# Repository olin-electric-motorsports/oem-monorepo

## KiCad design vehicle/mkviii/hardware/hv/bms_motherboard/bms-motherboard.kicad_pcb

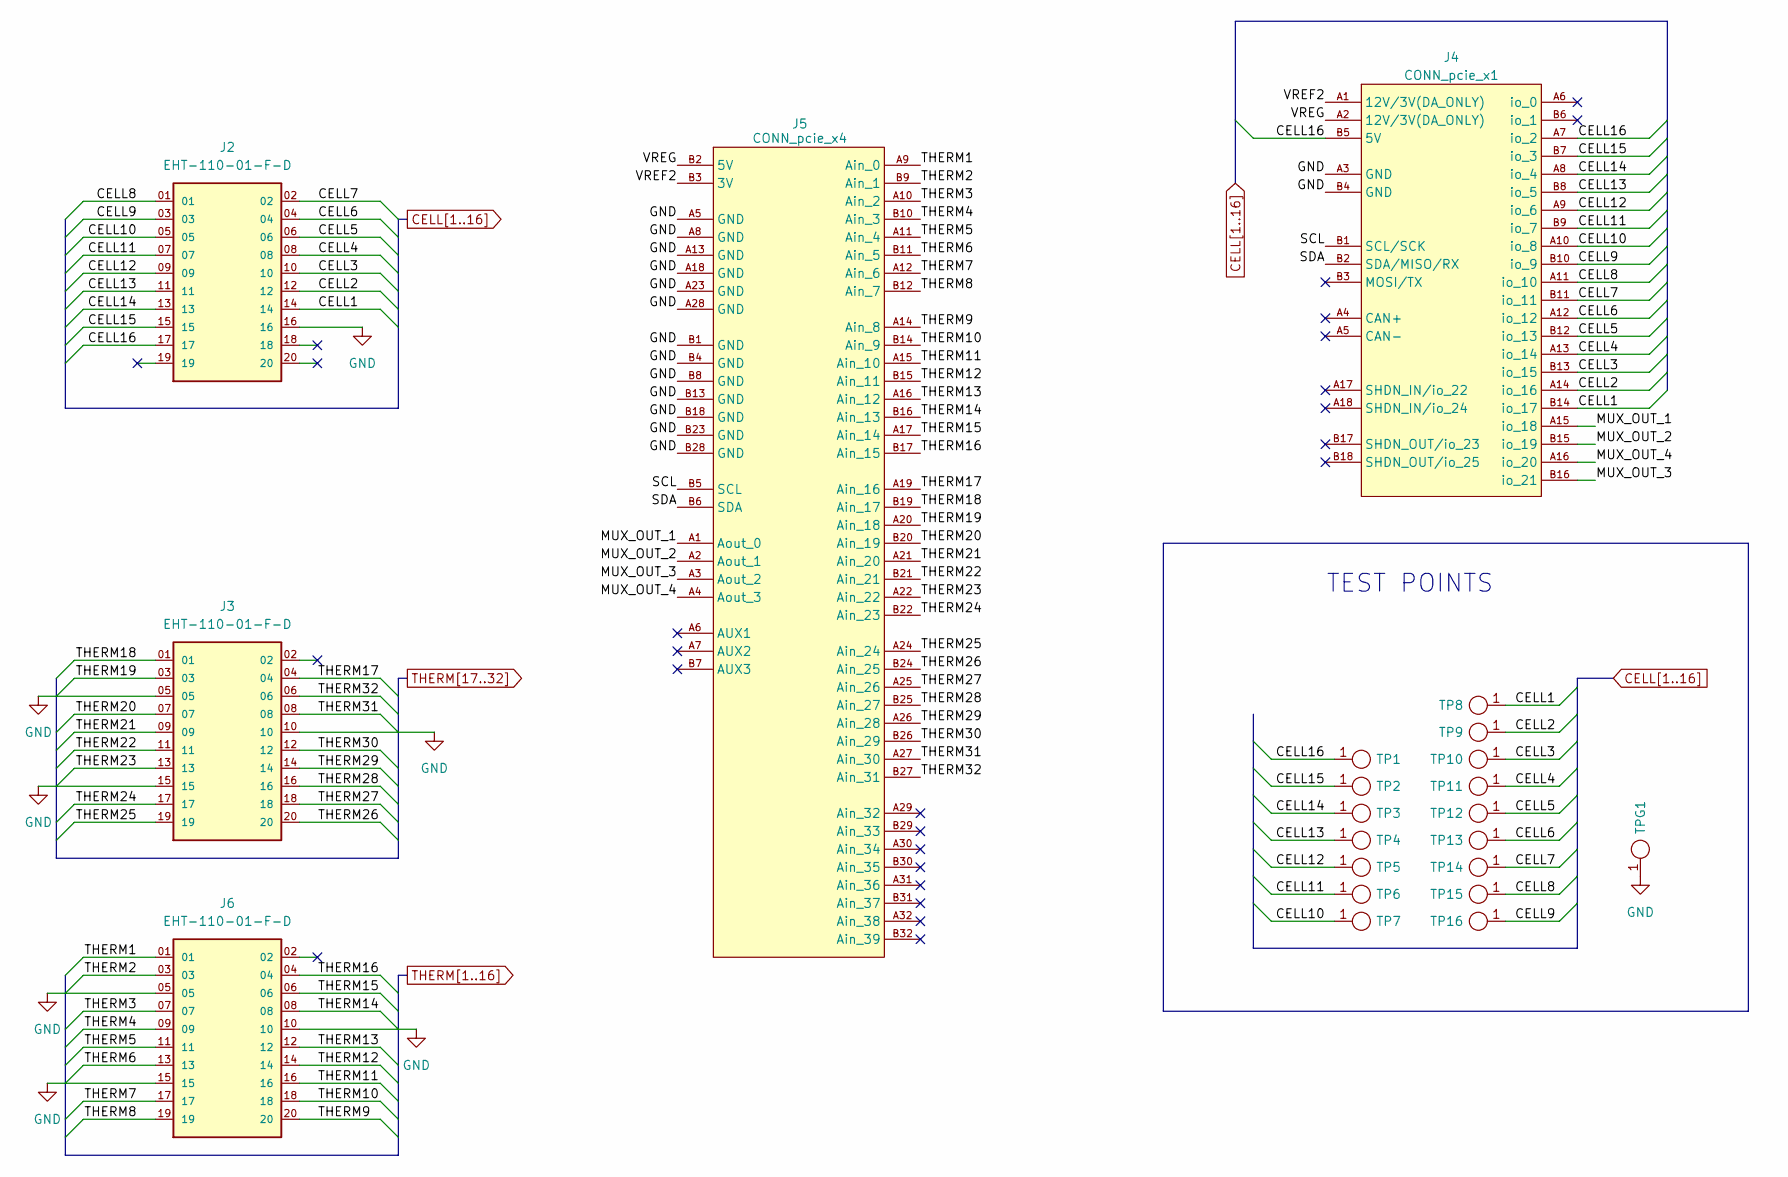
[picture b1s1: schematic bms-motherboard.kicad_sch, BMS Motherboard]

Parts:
J2, J3, J6: EHT-110-01-F-D; SAMTEC_EHT-110-01-X-D (J_EHT-110-01-F-D); MPN EHT-110-01-F-D
J4: CONN_pcie_x1; te_pcie_x1_connector
J5: CONN_pcie_x4; te_pcie_x4_connector
TP1, TP2, TP3, TP4, TP5, TP6, TP7, TP8, TP9, TP10, TP11, TP12, TP13, TP14, TP15, TP16: TP_SMD; Test_Point_SMD; MPN 5019
TPG1: TP_SMD; Test_Point_SMD; MPN 5019

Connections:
/MUX_OUT_1: J4.A15 (io_18), J5.A1 (Aout_0)
/MUX_OUT_2: J4.B15 (io_19), J5.A2 (Aout_1)
/MUX_OUT_3: J4.B16 (io_21), J5.A3 (Aout_2)
/MUX_OUT_4: J4.A16 (io_20), J5.A4 (Aout_3)
/SCL: J4.B1 (SCL/SCK), J5.B5 (SCL)
/SDA: J4.B2 (SDA/MISO/RX), J5.B6 (SDA)
/VREF2: J4.A1 (12V/3V(DA_ONLY)), J5.B3 (3V)
/VREG: J4.A2 (12V/3V(DA_ONLY)), J5.B2 (5V)
CELL1: J2.14, J4.B14 (io_17), TP8.1
CELL2: J2.12, J4.A14 (io_16), TP9.1
CELL3: J2.10, J4.B13 (io_15), TP10.1
CELL4: J2.08, J4.A13 (io_14), TP11.1
CELL5: J2.06, J4.B12 (io_13), TP12.1
CELL6: J2.04, J4.A12 (io_12), TP13.1
CELL7: J2.02, J4.B11 (io_11), TP14.1
CELL8: J2.01, J4.A11 (io_10), TP15.1
CELL9: J2.03, J4.B10 (io_9), TP16.1
CELL10: J2.05, J4.A10 (io_8), TP7.1
CELL11: J2.07, J4.B9 (io_7), TP6.1
CELL12: J2.09, J4.A9 (io_6), TP5.1
CELL13: J2.11, J4.B8 (io_5), TP4.1
CELL14: J2.13, J4.A8 (io_4), TP3.1
CELL15: J2.15, J4.B7 (io_3), TP2.1
CELL16: J2.17, J4.A7 (io_2), J4.B5 (5V), TP1.1
GND: J2.16, J3.05, J3.10, J3.15, J4.A3 (GND), J4.B4 (GND), J5.A5 (GND), J5.A8 (GND), J5.A13 (GND), J5.A18 (GND), J5.A23 (GND), J5.A28 (GND), J5.B1 (GND), J5.B4 (GND), J5.B8 (GND), J5.B13 (GND), J5.B18 (GND), J5.B23 (GND), J5.B28 (GND), J6.05, J6.10, J6.15, TPG1.1
THERM1: J5.A9 (Ain_0), J6.01
THERM2: J5.B9 (Ain_1), J6.03
THERM3: J5.A10 (Ain_2), J6.07
THERM4: J5.B10 (Ain_3), J6.09
THERM5: J5.A11 (Ain_4), J6.11
THERM6: J5.B11 (Ain_5), J6.13
THERM7: J5.A12 (Ain_6), J6.17
THERM8: J5.B12 (Ain_7), J6.19
THERM9: J5.A14 (Ain_8), J6.20
THERM10: J5.B14 (Ain_9), J6.18
THERM11: J5.A15 (Ain_10), J6.16
THERM12: J5.B15 (Ain_11), J6.14
THERM13: J5.A16 (Ain_12), J6.12
THERM14: J5.B16 (Ain_13), J6.08
THERM15: J5.A17 (Ain_14), J6.06
THERM16: J5.B17 (Ain_15), J6.04
THERM17: J3.04, J5.A19 (Ain_16)
THERM18: J3.01, J5.B19 (Ain_17)
THERM19: J3.03, J5.A20 (Ain_18)
THERM20: J3.07, J5.B20 (Ain_19)
THERM21: J3.09, J5.A21 (Ain_20)
THERM22: J3.11, J5.B21 (Ain_21)
THERM23: J3.13, J5.A22 (Ain_22)
THERM24: J3.17, J5.B22 (Ain_23)
THERM25: J3.19, J5.A24 (Ain_24)
THERM26: J3.20, J5.B24 (Ain_25)
THERM27: J3.18, J5.A25 (Ain_26)
THERM28: J3.16, J5.B25 (Ain_27)
THERM29: J3.14, J5.A26 (Ain_28)
THERM30: J3.12, J5.B26 (Ain_29)
THERM31: J3.08, J5.A27 (Ain_30)
THERM32: J3.06, J5.B27 (Ain_31)

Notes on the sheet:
TEST POINTS

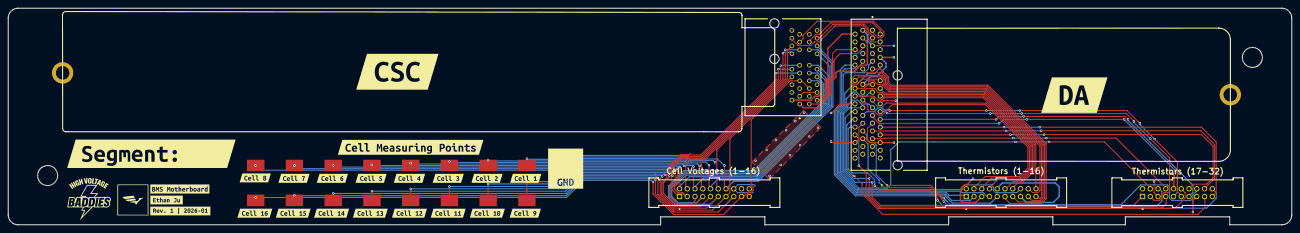
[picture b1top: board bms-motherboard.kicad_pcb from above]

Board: 2 copper layers, 331.3 x 55.9 mm, 48 parts (0 on the bottom side), 57 nets.

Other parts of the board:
H1, H2: CONN_MountingHole; PCIe_Mount
kibuzzard-691BC298: G***; kibuzzard-691BC298
kibuzzard-6747A1EF: G***; kibuzzard-6747A1EF
kibuzzard-6747A1F5: G***; kibuzzard-6747A1F5
kibuzzard-6747A1FA: G***; kibuzzard-6747A1FA
kibuzzard-6747A20D: G***; kibuzzard-6747A20D
kibuzzard-6747A21A: G***; kibuzzard-6747A21A
kibuzzard-6747A21D: G***; kibuzzard-6747A21D
kibuzzard-6747A22C: G***; kibuzzard-6747A22C
kibuzzard-6747A22F: G***; kibuzzard-6747A22F
kibuzzard-6747A069: G***; kibuzzard-6747A069
kibuzzard-6747A200: G***; kibuzzard-6747A200
kibuzzard-6747A204: G***; kibuzzard-6747A204
kibuzzard-6747A209: G***; kibuzzard-6747A209
kibuzzard-6747A211: G***; kibuzzard-6747A211
kibuzzard-6747A215: G***; kibuzzard-6747A215
kibuzzard-6747A222: G***; kibuzzard-6747A222
kibuzzard-6747A229: G***; kibuzzard-6747A229
kibuzzard-6747A319: G***; kibuzzard-6747A319
kibuzzard-6747A384: G***; kibuzzard-6747A384
kibuzzard-6747F2A5: G***; kibuzzard-6747F2A5
kibuzzard-67479E66: G***; kibuzzard-67479E66
kibuzzard-67479E86: G***; kibuzzard-67479E86
kibuzzard-69836BC9: G***; kibuzzard-69836BC9
kibuzzard-69836C11: G***; kibuzzard-69836C11

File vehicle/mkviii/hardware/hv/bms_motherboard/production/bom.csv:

Designator,Footprint,Quantity,Value,LCSC Part #
"J2, J3, J6",SAMTEC_EHT-110-01-X-D (J_EHT-110-01-F-D),3,EHT-110-01-F-D,EHT-110-01-F-D
J4,te_pcie_x1_connector,1,CONN_pcie_x1,
J5,te_pcie_x4_connector,1,CONN_pcie_x4,
"TP1, TP10, TP11, TP12, TP13, TP14, TP15, TP16, TP2, TP3, TP4, TP5, TP6, TP7, TP8, TP9, TPG1",Test_Point_SMD,17,TP_SMD,5019

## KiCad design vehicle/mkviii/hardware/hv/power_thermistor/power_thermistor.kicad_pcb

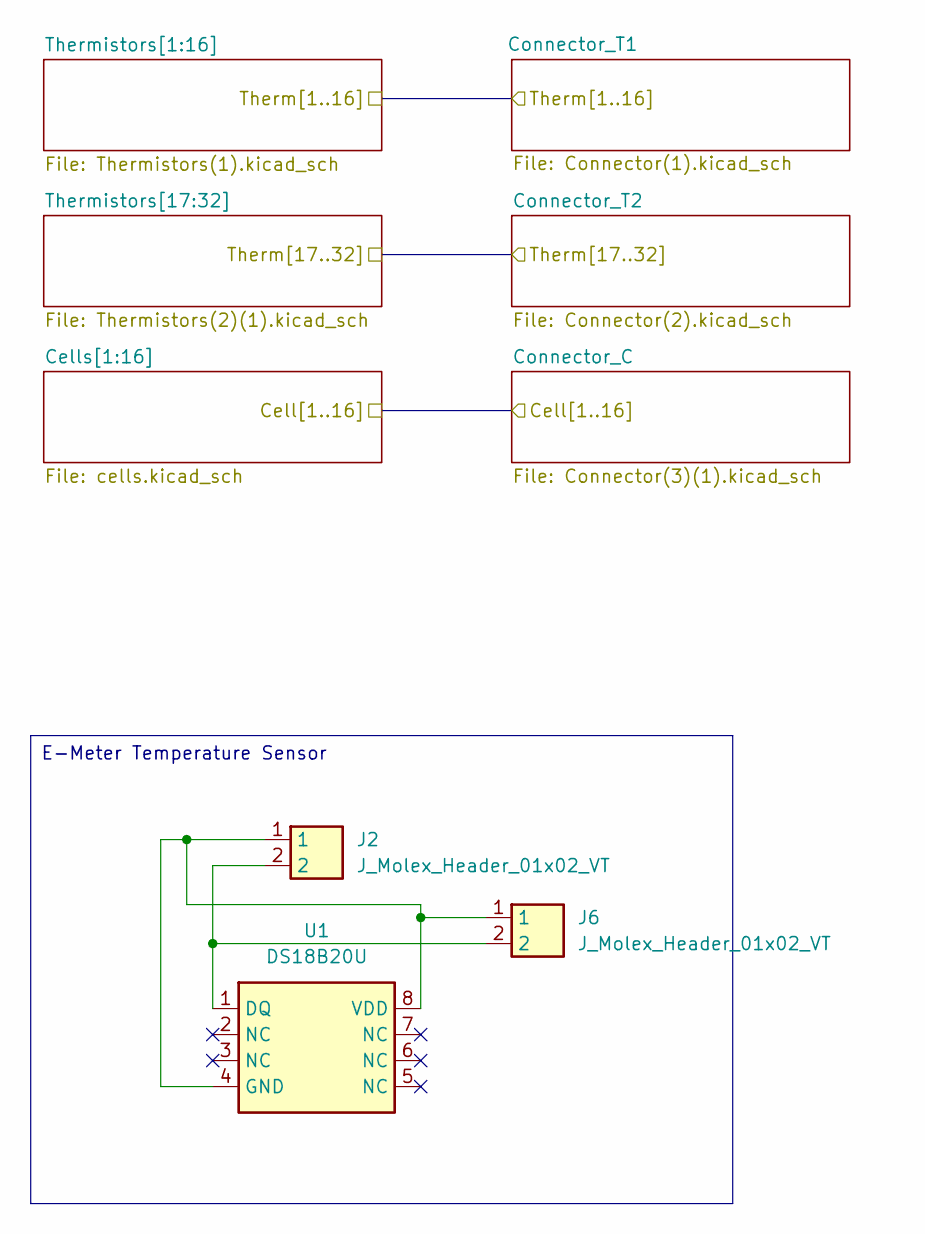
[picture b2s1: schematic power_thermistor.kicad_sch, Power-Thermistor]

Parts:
J2, J6: J_Molex_Header_01x02_VT; J_Molex_Header_01x02_VT - 43045-02YY_121314; MPN 43045-0212
U1: DS18B20U; 8-uSOP; MPN DS18B20U

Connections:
unnamed: J2.2, J6.2, U1.1 (DQ)
unnamed: J2.1, J6.1, U1.4 (GND), U1.8 (VDD)

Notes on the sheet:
E-Meter Temperature Sensor

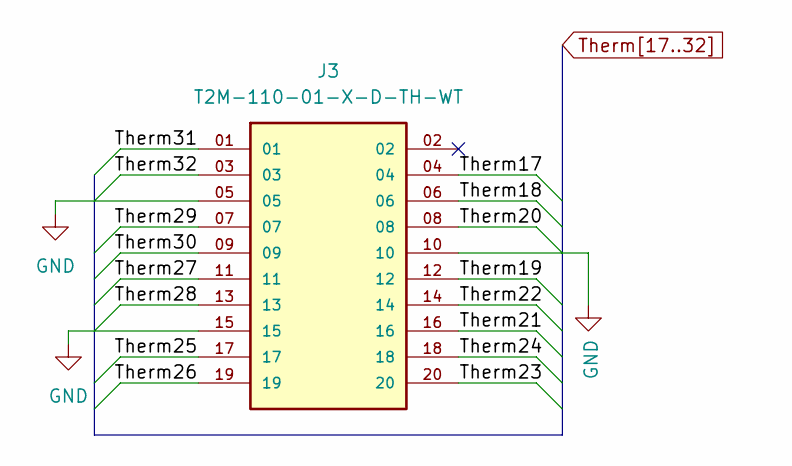
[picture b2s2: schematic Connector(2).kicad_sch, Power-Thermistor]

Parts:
J3: T2M-110-01-X-D-TH-WT; SAMTEC_EHT-110-01-X-D (J_EHT-110-01-F-D); PARTREV AH

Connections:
GND: J3.05, J3.10, J3.15; also elsewhere on the board
Therm17: J3.04; also elsewhere on the board
Therm18: J3.06; also elsewhere on the board
Therm19: J3.12; also elsewhere on the board
Therm20: J3.08; also elsewhere on the board
Therm21: J3.16; also elsewhere on the board
Therm22: J3.14; also elsewhere on the board
Therm23: J3.20; also elsewhere on the board
Therm24: J3.18; also elsewhere on the board
Therm25: J3.17; also elsewhere on the board
Therm26: J3.19; also elsewhere on the board
Therm27: J3.11; also elsewhere on the board
Therm28: J3.13; also elsewhere on the board
Therm29: J3.07; also elsewhere on the board
Therm30: J3.09; also elsewhere on the board
Therm31: J3.01; also elsewhere on the board
Therm32: J3.03; also elsewhere on the board

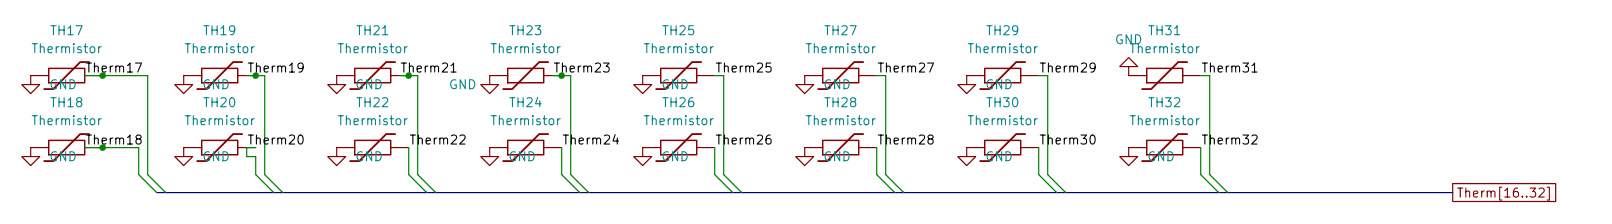
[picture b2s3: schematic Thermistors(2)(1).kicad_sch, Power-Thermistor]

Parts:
TH17, TH18, TH19, TH20, TH21, TH22, TH23, TH24, TH25, TH26, TH27, TH28, TH29, TH30, TH31, TH32: Thermistor; R_0603_1608Metric

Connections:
GND: TH17.1, TH18.1, TH19.1, TH20.1, TH21.1, TH22.1, TH23.1, TH24.1, TH25.1, TH26.1, TH27.1, TH28.1, TH29.1, TH30.1, TH31.1, TH32.1; also elsewhere on the board
Therm17: TH17.2; also elsewhere on the board
Therm18: TH18.2; also elsewhere on the board
Therm19: TH19.2; also elsewhere on the board
Therm20: TH20.2; also elsewhere on the board
Therm21: TH21.2; also elsewhere on the board
Therm22: TH22.2; also elsewhere on the board
Therm23: TH23.2; also elsewhere on the board
Therm24: TH24.2; also elsewhere on the board
Therm25: TH25.2; also elsewhere on the board
Therm26: TH26.2; also elsewhere on the board
Therm27: TH27.2; also elsewhere on the board
Therm28: TH28.2; also elsewhere on the board
Therm29: TH29.2; also elsewhere on the board
Therm30: TH30.2; also elsewhere on the board
Therm31: TH31.2; also elsewhere on the board
Therm32: TH32.2; also elsewhere on the board

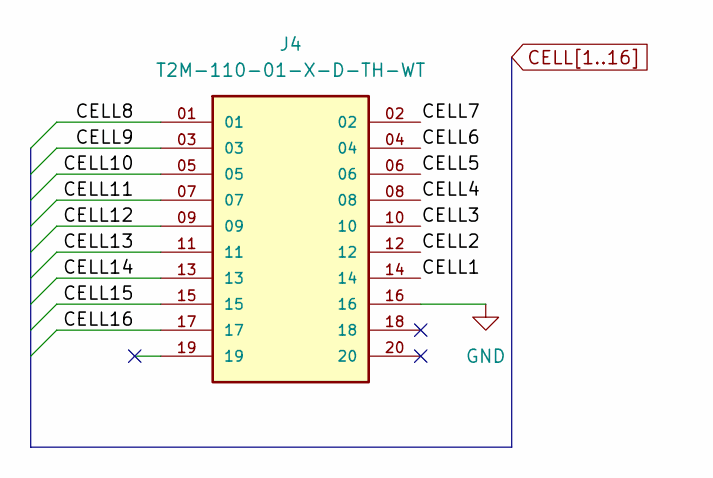
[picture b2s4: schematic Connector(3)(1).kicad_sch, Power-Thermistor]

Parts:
J4: T2M-110-01-X-D-TH-WT; SAMTEC_EHT-110-01-X-D (J_EHT-110-01-F-D); PARTREV AH

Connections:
CELL1: J4.14; also elsewhere on the board
CELL2: J4.12; also elsewhere on the board
CELL3: J4.10; also elsewhere on the board
CELL4: J4.08; also elsewhere on the board
CELL5: J4.06; also elsewhere on the board
CELL6: J4.04; also elsewhere on the board
CELL7: J4.02; also elsewhere on the board
CELL8: J4.01; also elsewhere on the board
CELL9: J4.03; also elsewhere on the board
CELL10: J4.05; also elsewhere on the board
CELL11: J4.07; also elsewhere on the board
CELL12: J4.09; also elsewhere on the board
CELL13: J4.11; also elsewhere on the board
CELL14: J4.13; also elsewhere on the board
CELL15: J4.15; also elsewhere on the board
CELL16: J4.17; also elsewhere on the board
GND: J4.16; also elsewhere on the board

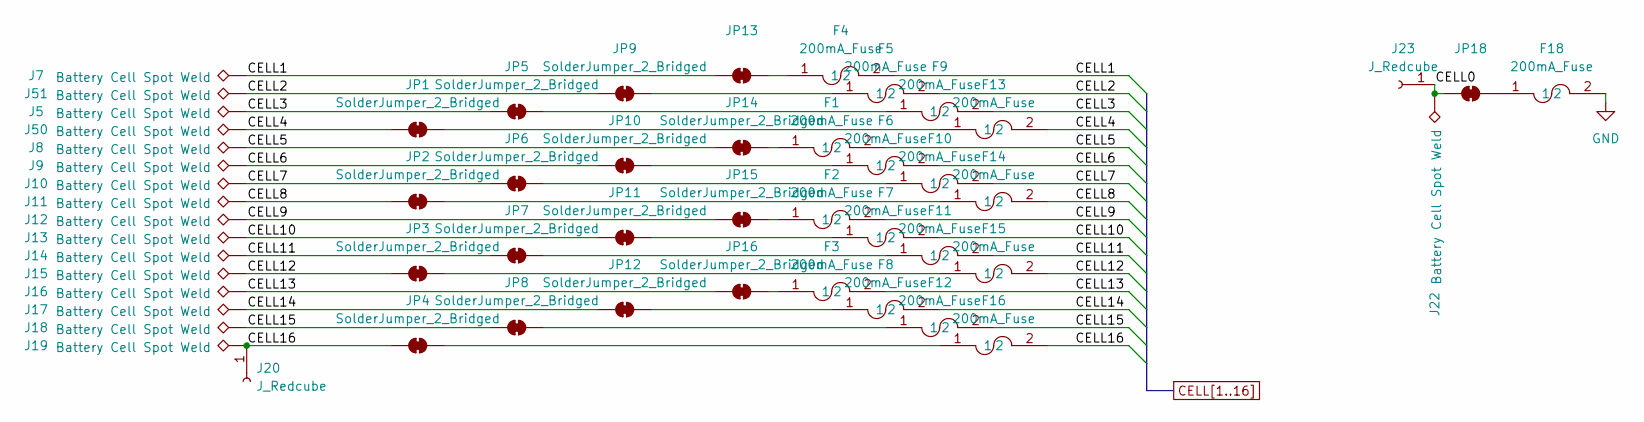
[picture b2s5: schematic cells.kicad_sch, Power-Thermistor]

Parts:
F1, F2, F3, F4, F5, F6, F7, F8, F9, F10, F11, F12, F13, F14, F15, F16, F18: 200mA_Fuse; Fuse_0805_2012Metric; MPN 507-1767-1-ND
J5, J7, J8, J9, J10, J11, J12, J13, J14, J15, J16, J17, J18, J19, J22, J50, J51: Battery Cell Spot Weld; J_Bond_Pad_4p
J20, J23: J_Redcube; Wurth-7461115; MPN 7461115
JP1, JP2, JP3, JP4, JP5, JP6, JP7, JP8, JP9, JP10, JP11, JP12, JP13, JP14, JP15, JP16, JP18: SolderJumper_2_Bridged; SolderJumper-2_P1.3mm_Bridged2Bar_Pad1.0x1.5mm

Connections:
/Cells[1:16]/CELL0: J22.1, J23.1, JP18.1 (A)
CELL1: F4.2, J7.1, JP13.1 (A); also elsewhere on the board
CELL2: F5.2, J51.1, JP9.1 (A); also elsewhere on the board
CELL3: F9.2, J5.1, JP5.1 (A); also elsewhere on the board
CELL4: F13.2, J50.1, JP1.1 (A); also elsewhere on the board
CELL5: F1.2, J8.1, JP14.1 (A); also elsewhere on the board
CELL6: F6.2, J9.1, JP10.1 (A); also elsewhere on the board
CELL7: F10.2, J10.1, JP6.1 (A); also elsewhere on the board
CELL8: F14.2, J11.1, JP2.1 (A); also elsewhere on the board
CELL9: F2.2, J12.1, JP15.1 (A); also elsewhere on the board
CELL10: F7.2, J13.1, JP11.1 (A); also elsewhere on the board
CELL11: F11.2, J14.1, JP7.1 (A); also elsewhere on the board
CELL12: F15.2, J15.1, JP3.1 (A); also elsewhere on the board
CELL13: F3.2, J16.1, JP16.1 (A); also elsewhere on the board
CELL14: F8.2, J17.1, JP12.1 (A); also elsewhere on the board
CELL15: F12.2, J18.1, JP8.1 (A); also elsewhere on the board
CELL16: F16.2, J19.1, J20.1, JP4.1 (A); also elsewhere on the board
GND: F18.2; also elsewhere on the board
unnamed: F13.1, JP1.2 (B)
unnamed: F14.1, JP2.2 (B)
unnamed: F15.1, JP3.2 (B)
unnamed: F16.1, JP4.2 (B)
unnamed: F9.1, JP5.2 (B)
unnamed: F10.1, JP6.2 (B)
unnamed: F11.1, JP7.2 (B)
unnamed: F12.1, JP8.2 (B)
unnamed: F5.1, JP9.2 (B)
unnamed: F6.1, JP10.2 (B)
unnamed: F7.1, JP11.2 (B)
unnamed: F8.1, JP12.2 (B)
unnamed: F4.1, JP13.2 (B)
unnamed: F1.1, JP14.2 (B)
unnamed: F2.1, JP15.2 (B)
unnamed: F3.1, JP16.2 (B)
unnamed: F18.1, JP18.2 (B)

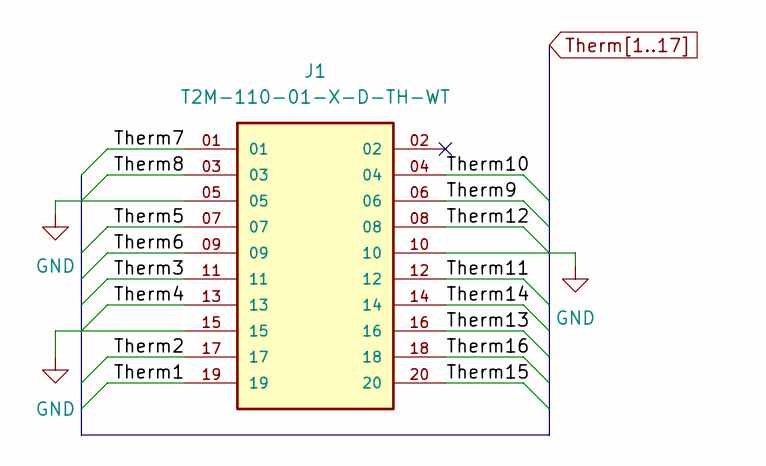
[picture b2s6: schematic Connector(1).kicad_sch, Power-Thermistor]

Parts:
J1: T2M-110-01-X-D-TH-WT; SAMTEC_EHT-110-01-X-D (J_EHT-110-01-F-D); PARTREV AH

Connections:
GND: J1.05, J1.10, J1.15; also elsewhere on the board
Therm1: J1.19; also elsewhere on the board
Therm2: J1.17; also elsewhere on the board
Therm3: J1.11; also elsewhere on the board
Therm4: J1.13; also elsewhere on the board
Therm5: J1.07; also elsewhere on the board
Therm6: J1.09; also elsewhere on the board
Therm7: J1.01; also elsewhere on the board
Therm8: J1.03; also elsewhere on the board
Therm9: J1.06; also elsewhere on the board
Therm10: J1.04; also elsewhere on the board
Therm11: J1.12; also elsewhere on the board
Therm12: J1.08; also elsewhere on the board
Therm13: J1.16; also elsewhere on the board
Therm14: J1.14; also elsewhere on the board
Therm15: J1.20; also elsewhere on the board
Therm16: J1.18; also elsewhere on the board

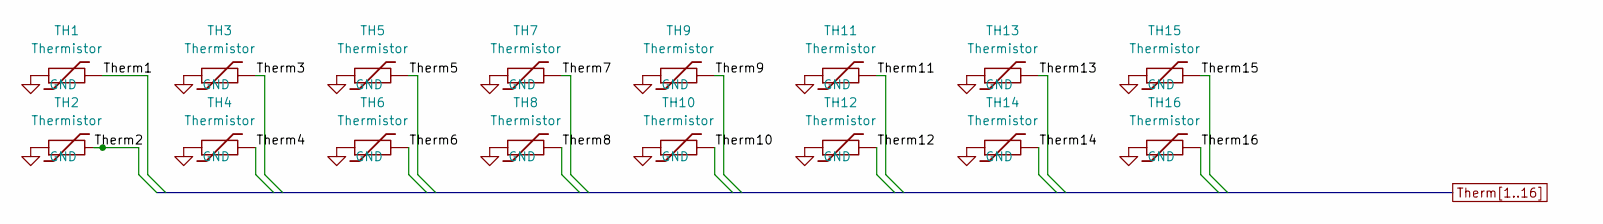
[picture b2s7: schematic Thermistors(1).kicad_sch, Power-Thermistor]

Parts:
TH1, TH2, TH3, TH4, TH5, TH6, TH7, TH8, TH9, TH10, TH11, TH12, TH13, TH14, TH15, TH16: Thermistor; R_0603_1608Metric

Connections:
GND: TH1.1, TH2.1, TH3.1, TH4.1, TH5.1, TH6.1, TH7.1, TH8.1, TH9.1, TH10.1, TH11.1, TH12.1, TH13.1, TH14.1, TH15.1, TH16.1; also elsewhere on the board
Therm1: TH1.2; also elsewhere on the board
Therm2: TH2.2; also elsewhere on the board
Therm3: TH3.2; also elsewhere on the board
Therm4: TH4.2; also elsewhere on the board
Therm5: TH5.2; also elsewhere on the board
Therm6: TH6.2; also elsewhere on the board
Therm7: TH7.2; also elsewhere on the board
Therm8: TH8.2; also elsewhere on the board
Therm9: TH9.2; also elsewhere on the board
Therm10: TH10.2; also elsewhere on the board
Therm11: TH11.2; also elsewhere on the board
Therm12: TH12.2; also elsewhere on the board
Therm13: TH13.2; also elsewhere on the board
Therm14: TH14.2; also elsewhere on the board
Therm15: TH15.2; also elsewhere on the board
Therm16: TH16.2; also elsewhere on the board

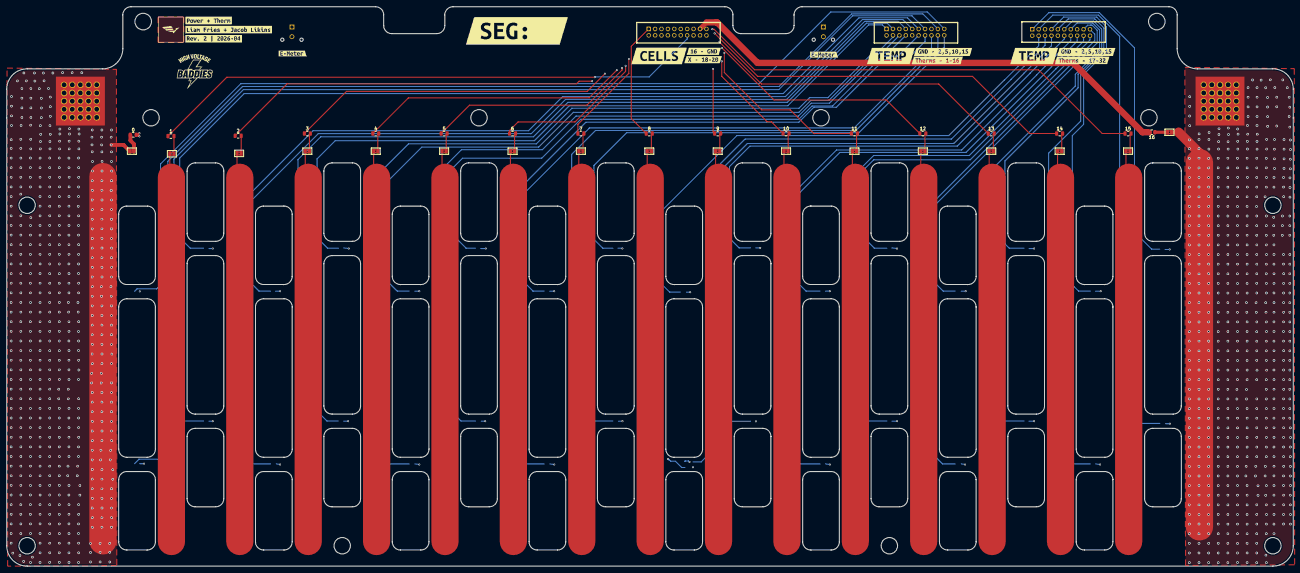
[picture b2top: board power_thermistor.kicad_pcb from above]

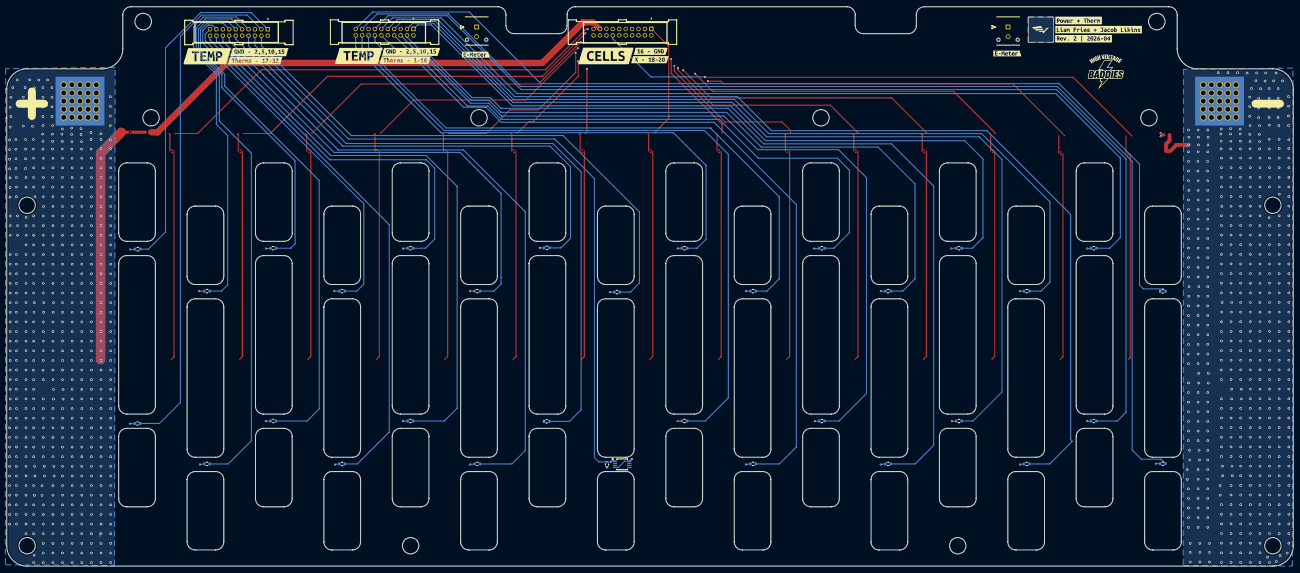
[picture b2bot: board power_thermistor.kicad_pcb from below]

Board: 4 copper layers, 400.9 x 174.3 mm, 120 parts (54 on the bottom side), 69 nets.

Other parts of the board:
kibuzzard-69DFA9BC, kibuzzard-69DFA9BC#2: G***; kibuzzard-69DFA9BC
kibuzzard-69E00A54, kibuzzard-69E00A54#2, kibuzzard-69E00A54#3, kibuzzard-69E00A54#4: G***; kibuzzard-69E00A54
kibuzzard-69E05987, kibuzzard-69E05987#2: G***; kibuzzard-69E05987
kibuzzard-6738FA22, kibuzzard-6738FA22#2: G***; kibuzzard-6738FA22
kibuzzard-6738FB72, kibuzzard-6738FB72#2, kibuzzard-6738FB72#3, kibuzzard-6738FB72#4: G***; kibuzzard-6738FB72
kibuzzard-69840BF2, kibuzzard-69840BF2#2: G***; kibuzzard-69840BF2
kibuzzard-69840BF7, kibuzzard-69840BF7#2: G***; kibuzzard-69840BF7
kibuzzard-69840C1E, kibuzzard-69840C1E#2: G***; kibuzzard-69840C1E
kibuzzard-69840C4F, kibuzzard-69840C4F#2: G***; kibuzzard-69840C4F
kibuzzard-69840C62, kibuzzard-69840C62#2: G***; kibuzzard-69840C62
kibuzzard-69840C71, kibuzzard-69840C71#2: G***; kibuzzard-69840C71
kibuzzard-6739182D: G***; kibuzzard-6739182D
kibuzzard-67390047, kibuzzard-67390047#2: G***; kibuzzard-67390047

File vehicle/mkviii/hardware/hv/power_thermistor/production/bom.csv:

Designator,Footprint,Quantity,Value,LCSC Part #
"F1, F10, F11, F12, F13, F14, F15, F16, F18, F2, F3, F4, F5, F6, F7, F8, F9",0805,17,200mA_Fuse,507-1767-1-ND
"J1, J3, J4",SAMTEC_EHT-110-01-X-D (J_EHT-110-01-F-D),3,T2M-110-01-X-D-TH-WT,
"J10, J11, J12, J13, J14, J15, J16, J17, J18, J19, J22, J5, J50, J51, J7, J8, J9",J_Bond_Pad_4p,17,Battery Cell Spot Weld,
"J2, J6",J_Molex_Header_01x02_VT - 43045-02YY_121314,2,J_Molex_Header_01x02_VT,43045-0212
"J20, J23",J_Wurth_7461115,2,J_Redcube,7461115
"TH1, TH10, TH11, TH12, TH13, TH14, TH15, TH16, TH17, TH18, TH19, TH2, TH20, TH21, TH22, TH23, TH24, TH25, TH26, TH27, TH28, TH29, TH3, TH30, TH31, TH32, TH4, TH5, TH6, TH7, TH8, TH9",0603,32,Thermistor,
U1,8-uSOP,1,DS18B20U,DS18B20U

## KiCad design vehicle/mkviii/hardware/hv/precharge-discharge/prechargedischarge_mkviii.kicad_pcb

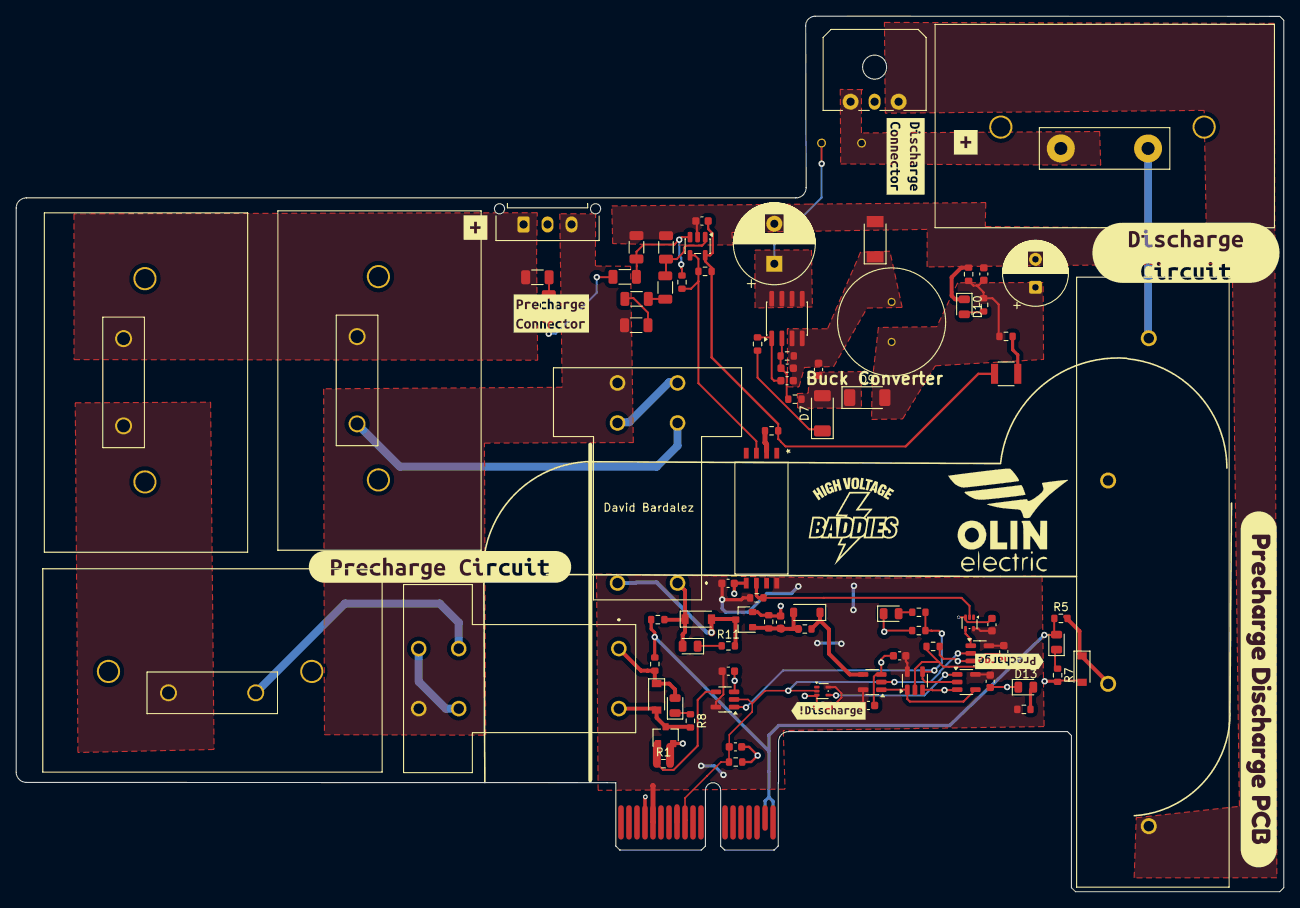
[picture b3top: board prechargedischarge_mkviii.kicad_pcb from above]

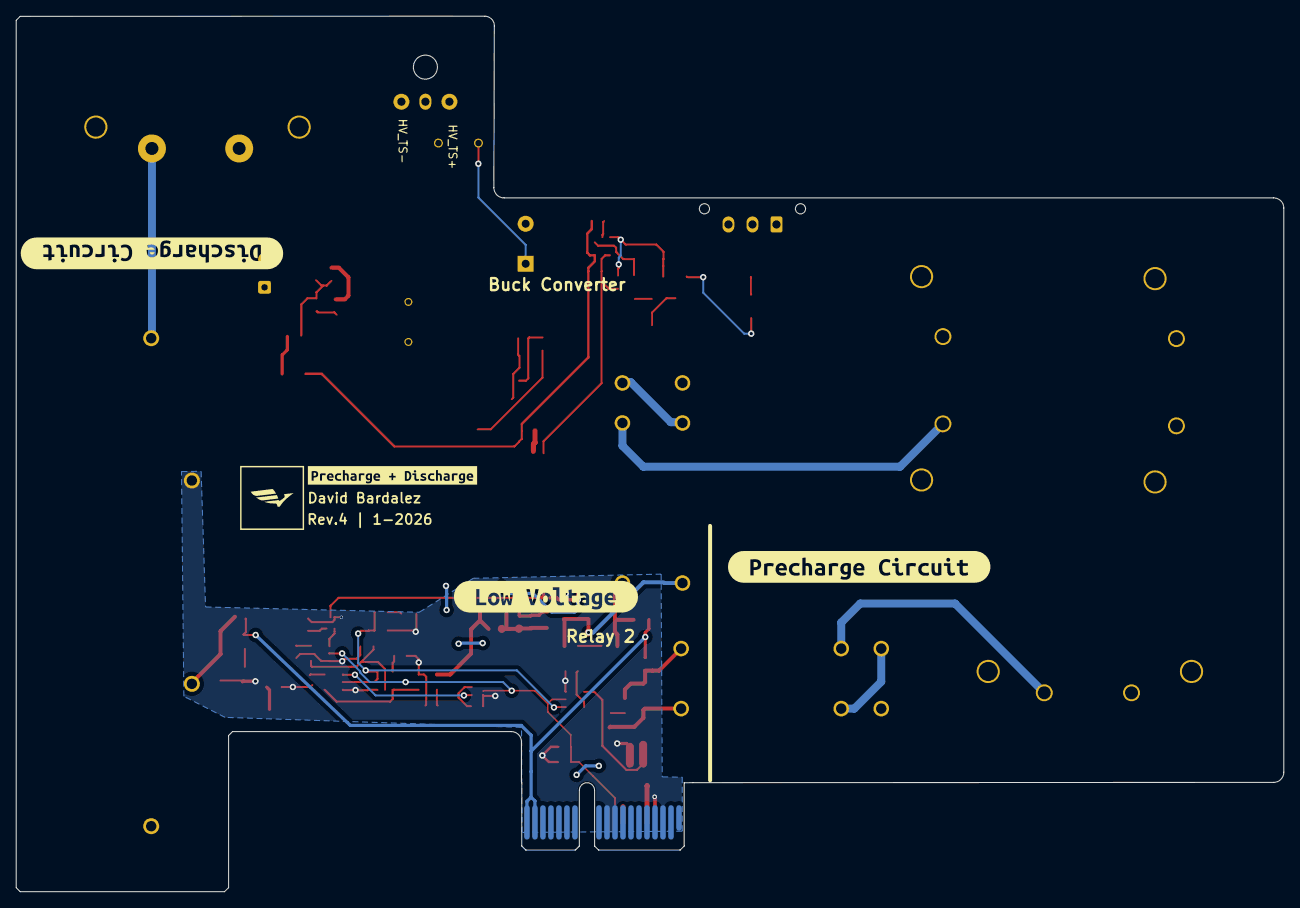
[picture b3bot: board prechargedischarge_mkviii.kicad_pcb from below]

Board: 2 copper layers, 158.4 x 109.4 mm, 100 parts (4 on the bottom side), 51 nets.

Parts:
C1, C5, C6, C10, C12, C13, C14, C15, C16: 0.1 µF; C_0603_1608Metric
C2, C11: C_2.2uF; C_0603_1608Metric
C3: C_470pF; C_0603_1608Metric
C4: C_.22uF; C_0603_1608Metric
C7: 100uF+; CP_Radial_D8.0mm_P3.50mm
C8, C17: C_1uF; C_0603_1608Metric
C9: 10uF+; CP_Radial_D10.0mm_P5.00mm
D1, D3, D6: SS110LW; D_SOD-123
D2, D4, D5, D10, D12, D13: LED_WHITE; D_0805_2012Metric
D7, D8, D9: STTH1R06AF; D_SOD-128
D11: 1N4148W; D_SOD-123
F1: F_21mA_420V
F2: F_500mA_16V; Fuse_1210
J2: Conn_01x03_Pin; Molex_Micro-Fit_3.0_43650-0300_1x03_P3.00mm_Horizontal
J3: CONN_pcie_x1; pcie_x1
J4: Conn_01x03_Pin; Molex_Micro-Fit_3.0_43650-0315_1x03_P3.00mm_Vertical
K1, K3: G2RG-2A-X_DC12; K_Relay_DPST_NO_10A_12V_TH
K2: 3350-4275-126; Relay_Comus_3350
L1: L_1.2mH
Q1, Q2: SSM3K333R; SOT-23F
R1, R28, R32: R_10K; R_0603_1608Metric
R2, R5, R10: 12R; R_0603_1608Metric
R3, R4: 560R-100W; R_TO247-Heatsink
R6: 3KR-100W; R_TO247-Heatsink
R7, R8, R11, R24, R27, R30: 1KR; R_0603_1608Metric
R9: 120R-100W; R_TO247-Heatsink
R12: 270kR; R_0603
R13, R14, R17, R18: 2.2 MΩ; R_1206_3216Metric
R15, R19: 330 kΩ; R_1206_3216Metric
R16: 36 kΩ; R_1206_3216Metric
R20: 25 kΩ; R_1206_3216Metric
R21: R_71.5K; R_0603_1608Metric
R22: R_6.04K; R_0603_1608Metric
R23: R_3K; R_0603_1608Metric
R25: R_0_2512; R_0603_1608Metric
R26: 330Ω; R_0603_1608Metric
R29: R_4.7M; R_0603_1608Metric
R31: R_71.5k; R_0603_1608Metric
R33, R36: R_10k; R_0603_1608Metric
R34, R35: 100 kΩ; R_0603_1608Metric
U1, U6: U_GATE_SN74LVC1G02DBVR; SOT-23-5
U2: LM397; SOT-23-5
U3: MP9488; SOIC-8_3.9x4.9mm_P1.27mm
U4: ACNT-H50L-500E
U5, U9: 74LVC1GU04DRL; SOT-553
U7, U8, U10: SN74LVC1G08DBVR; SOT-23-5
kibuzzard-679E7E49, kibuzzard-679E7E49#2: G***; kibuzzard-679E7E49
kibuzzard-679E7E71: G***; kibuzzard-679E7E71
kibuzzard-679E7EA1: G***; kibuzzard-679E7EA1
kibuzzard-679E816B: G***; kibuzzard-679E816B
kibuzzard-679E8163: G***; kibuzzard-679E8163
kibuzzard-679E8270: G***; kibuzzard-679E8270
kibuzzard-679EBF0B, kibuzzard-679EBF0B#2: G***; kibuzzard-679EBF0B
kibuzzard-6784D6A3: G***; kibuzzard-6784D6A3
kibuzzard-6784D6E2: G***; kibuzzard-6784D6E2
kibuzzard-6784D698: G***; kibuzzard-6784D698
kibuzzard-639639B8: G***; kibuzzard-639639B8

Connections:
+5V: C5.1, C6.1, C10.1, C12.1, C13.1, C14.1, C15.1, C16.1, J3.B5 (5V), R27.1, R36.2, U1.5 (VCC), U4.8, U5.5 (VCC), U6.5 (VCC), U7.5 (VCC), U8.5 (VCC), U9.5 (VCC), U10.5 (VCC)
/+5V_TS_FUSED: C1.1, F2.1, R26.1, R33.2, U2.5 (V+)
/DONE_ISO: R36.1, U4.6, U5.2
/DONE_ISO_N: U5.4, U10.1
/DONE_ISO_SET: R35.2, U1.2 (in), U10.4
/DONE_LATCHED: U1.1 (in), U6.4 (out), U7.1
/DONE_LATCHED_N: R30.1, R32.1, U1.4 (out), U6.2 (in), U8.1
/FB: C3.1, R21.2, R22.1, U3.2 (FB)
/FINAL_SHUTDOWN: D2.2 (A), J3.A17 (SHDN_IN/io_22), J3.A18 (SHDN_IN/io_24), R2.1, R5.1, R10.1
/HV_BAT+: J4.1, R4.1, R9.1, R13.2
/HV_TS+: F1.2, J2.1, R6.1
/HV_TS+_Fuse: J4.3, K1.5 (NO_(-)), K3.5 (NO_(-)), R17.2
/HV_TS-: C1.2, C7.2, C8.2, C9.2, D8.2 (A), D10.1 (K), J2.3, K2.1, R16.2, R20.2, R23.2, U2.2 (V-)
/PRECHARGE_DONE_N: R29.1, R33.1, U2.4, U4.3
/PRECHARGE_LSD: C17.2, J3.B9 (io_7), R34.2, U7.2, U8.2, U9.2, U10.2
/PRECHARGE_LSD_1: Q1.1 (G), R1.1, U8.4
/PRECHARGE_LSD_2: D11.1 (K), R31.2, U7.4
/PRECHARGE_LSD_N: U6.1 (in), U9.4
/SW: C2.2, C3.2, C4.2, D8.1 (K), L1.1, R22.2, U3.3 (SW), U3.4 (SW)
/TS+_FUSED: C9.1, F1.1, U3.5 (NC), U3.6 (NC), U3.7 (VIN), U3.8 (NC)
/VCC: C2.1, R28.2, U3.1 (VCC)
/V_DC_SENSE: R15.1, R16.1, R29.2, U2.3 (+)
/V_PACK_SENSE: R19.1, R20.1, U2.1 (-)
GND: C5.2, C6.2, C10.2, C11.2, C12.2, C13.2, C14.2, C15.2, C16.2, C17.1, D3.2 (A), D12.1 (K), D13.1 (K), J3.A3 (GND), J3.A9 (io_6), J3.A10 (io_8), J3.B4 (GND), K2.3 (-), Q1.2 (S), Q2.2 (S), R1.2, R7.2, R12.2, R32.2, R34.1, R35.1, U1.3 (GND), U4.5, U5.3 (GND), U6.3 (GND), U7.3 (GND), U8.3 (GND), U9.3 (GND), U10.3 (GND)
unnamed: D1.2 (A), K1.8 (COIL_2), Q1.3 (D), R8.2
unnamed: D1.1 (K), D4.2 (A), K1.1 (COIL_1), R2.2
unnamed: D2.1 (K), R7.1
unnamed: D3.1 (K), K2.2 (+), R5.2
unnamed: D4.1 (K), R8.1
unnamed: D5.2 (A), D6.1 (K), K3.1 (COIL_1), R10.2
unnamed: D5.1 (K), R11.1
unnamed: D6.2 (A), K3.8 (COIL_2), Q2.3 (D), R11.2
unnamed: C4.1, D7.2 (A), D9.1 (K), R21.1
unnamed: D7.1 (K), R28.1
unnamed: C7.1, C8.1, D9.2 (A), L1.2, R23.1, R24.1, R25.2
unnamed: D10.2 (A), R24.2
unnamed: C11.1, D11.2 (A), Q2.1 (G), R12.1, R31.1
unnamed: D12.2 (A), R30.2
unnamed: D13.2 (A), R27.2
unnamed: F2.2, R25.1
unnamed: K1.4 (NO), K1.6 (COM)
unnamed: K1.3 (COM_(+)), R3.2
unnamed: K2.4, R6.2
unnamed: K3.4 (NO), K3.6 (COM)
unnamed: K3.3 (COM_(+)), R9.2
unnamed: R3.1, R4.2
unnamed: R13.1, R14.2
unnamed: R14.1, R15.2
unnamed: R17.1, R18.2
unnamed: R18.1, R19.2
unnamed: R26.2, U4.2
